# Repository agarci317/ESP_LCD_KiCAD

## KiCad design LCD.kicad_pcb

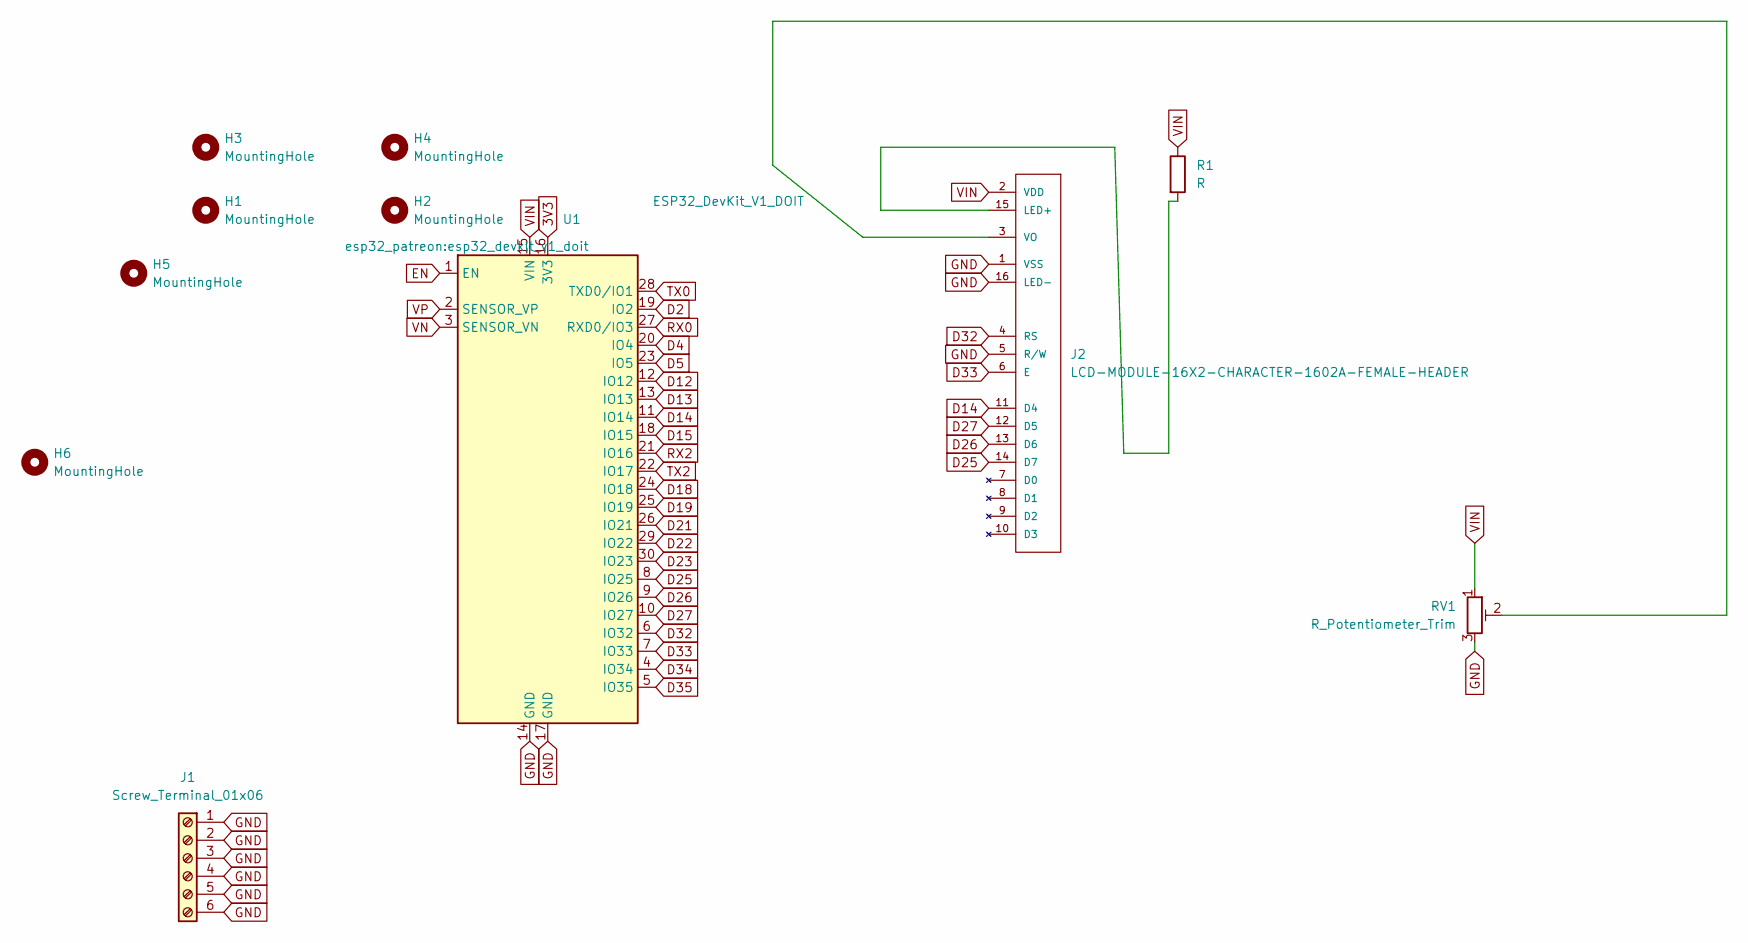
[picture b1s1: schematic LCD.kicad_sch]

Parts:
H1, H2, H3, H4, H5, H6: MountingHole; MountingHole_2.5mm
J1: Screw_Terminal_01x06; PhoenixContact_MSTBV_2,5_6-GF-5,08_1x06_P5.08mm_Vertical_Th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
J2: LCD-MODULE-16X2-CHARACTER-1602A-FEMALE-HEADER; LCD-1602A
R1: R; R_Axial_DIN0411_L9.9mm_D3.6mm_P25.40mm_Horizontal
RV1: R_Potentiometer_Trim; Potentiometer_Bourns_3006P_Horizontal
U1: ESP32_DevKit_V1_DOIT; esp32_devkit_v1_doit

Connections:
3V3: U1.16 (3V3)
D2: U1.19 (IO2)
D4: U1.20 (IO4)
D5: U1.23 (IO5)
D12: U1.12 (IO12)
D13: U1.13 (IO13)
D14: J2.11 (D4), U1.11 (IO14)
D15: U1.18 (IO15)
D18: U1.24 (IO18)
D19: U1.25 (IO19)
D21: U1.26 (IO21)
D22: U1.29 (IO22)
D23: U1.30 (IO23)
D25: J2.14 (D7), U1.8 (IO25)
D26: J2.13 (D6), U1.9 (IO26)
D27: J2.12 (D5), U1.10 (IO27)
D32: J2.4 (RS), U1.6 (IO32)
D33: J2.6 (E), U1.7 (IO33)
D34: U1.4 (IO34)
D35: U1.5 (IO35)
EN: U1.1 (EN)
GND: J1.1, J1.2, J1.3, J1.4, J1.5, J1.6, J2.1 (VSS), J2.5 (R/W), J2.16 (LED-), RV1.3, U1.14 (GND), U1.17 (GND)
unnamed: J2.3 (VO), RV1.2
unnamed: J2.15 (LED+), R1.2
RX0: U1.27 (RXD0/IO3)
RX2: U1.21 (IO16)
TX0: U1.28 (TXD0/IO1)
TX2: U1.22 (IO17)
VIN: J2.2 (VDD), R1.1, RV1.1, U1.15 (VIN)
VN: U1.3 (SENSOR_VN)
VP: U1.2 (SENSOR_VP)

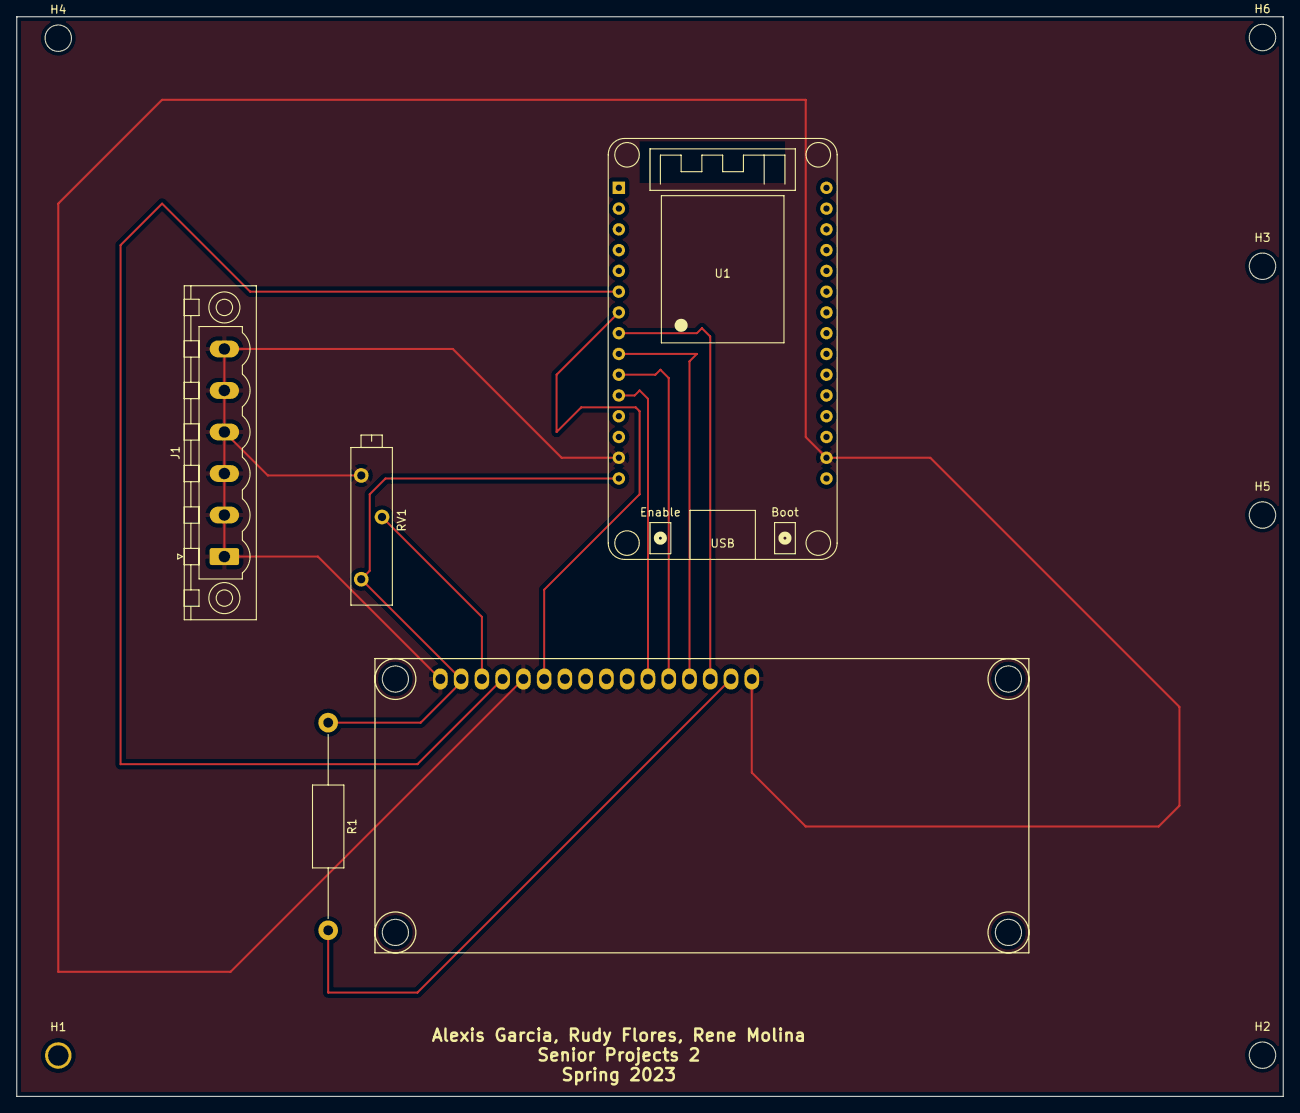
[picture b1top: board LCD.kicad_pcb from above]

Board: 2 copper layers, 154.9 x 132.1 mm, 11 parts (0 on the bottom side), 10 nets.
